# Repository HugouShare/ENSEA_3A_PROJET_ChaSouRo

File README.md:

# 🤖 ChaSouRo 🤖

## 📝 Rapport de projet

Pour consulter notre rapport de projet [cliquez ici](Documents/Rapport%20de%20projet.md)  

---

## 👨🏽 Équipe

<div align="left">

   **🙋‍♂️ [Hugo CARVALHO FONTES](https://github.com/HugouShare)**

   **🙋‍♂️ [Nelven THÉBAULT](https://github.com/NelvTheb)**

   **🙋‍♂️ [Hugo CORDI](https://github.com/Lynxlegrand)**

   **🙋‍♂️ [Arthur Cesar NJITCHOU NKWA](https://github.com/ArthurNjitchou)**

</div>

## ⚙️ Introduction

- Nous réalisons ce projet dans le cadre de notre dernière année d'étude en spécialité électronique et systèmes embarqués à l'[ENSEA](https://www.ensea.fr/fr) située à Cergy.
- Le but du projet est de réaliser deux robots : l'un étant le robot chat et l'autre le robot souris. Les deux robots évoluent ensuite de manière autonome sur une table. Le but du jeu est alors le suivant : le robot chat doit tenter d'attraper le robot souris qui doit donc tenter d'échapper au robot chat. Une fois que le robot chat attrape le robot souris, les rôles s'inversent et la partie continue. 

## 🎯 Missions & Objectifs

Les missions principales sont les suivantes (réparties selon différents niveaux) :
  - **Niveau 0 :**
    - Le robot se déplace
    - Il ne tombe pas de la table
  - **Niveau 1 :**
    - Il détecte et se dirige vers un objet
    - Ou s’en éloigne s’il n’est pas le chat
  - **Niveau 2 :**
    - Il change de comportement (proie/prédateur) après un contact
    - Il fonctionne avec plusieurs robots sur la table
  - **Niveau 3 :**
    - Il n’est pas affecté par les obstacles hors de la table
    - Il est donc capable de se localiser

Dans notre cas à nous, nous choisissons le niveau 1 voire potentiellement, selon notre avancement, le niveau 2.  

## ⌚ Timeline du projet  

```mermaid
%%{init: {"theme":"default", "themeVariables": {
  "primaryColor": "#4F46E5",
  "primaryTextColor": "#ffffff",
  "primaryBorderColor": "#312E81",
  "lineColor": "#6366F1",
  "secondaryColor": "#E0E7FF",
  "tertiaryColor": "#A5B4FC"
}}}%%

timeline
    section Phase 1 - conception du PCB
      Séance 1 : Point réunion + schéma architectural / BOM
      Séance 2 et 3 : Schéma électronique annoté
      Séance 4 : Corrections Schéma / BOM Finale
      Séance 5 : Point réunion + placement
      Séance 6 : Placement corrigé
      Séance 7 et 8 : Routage
      Séance 9 et 10 : Corrections Routage, export...
    section Phase 2 - mécanique 3D + prise en main et programmation des différents capteurs et actionneurs
      Séance 1 : Point réunion + architecture de subsomption + architecture schéma logicielle + soudure composants sur PCBs + vérification du bon fonctionnement des PCBs
      Séance 2 et 3 et 4 : Prise en main & programmation du LiDar + accéléromètre + écran OLED + module bluetooth avec développement application apk
      Séance 5 : Point réunion + vérification du bon fonctionnement des différents modules
      Séance 6 et 7 et 8 : Développement de l'odométrie + programmation des moteurs + 1x TOF puis 4x TOFs + modification de la structure mécanique du robot pour intégration des 4 TOFs et écran OLED
      Séance 9 et 10 : Impression 3D de la structure mécanique du robot + début de l'intégration des différents modules + finalisation de la programmation des 4x TOFs ensemble 
    section Phase 3 - Intégration, tests & vérifications
      Séance 1 et 2 : Point réunion + intégration, tests & vérifications
      Séance 3 : DEMONSTRATION FINALE
```

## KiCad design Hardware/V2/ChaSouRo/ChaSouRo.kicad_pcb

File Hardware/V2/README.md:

# Modifications sur la V1

- Problèmes sur la taille des empreintes pour les capacités >= 10uF -> Passage en 0603
- Changement pad sw wurth vers un connecteur (plus propre) -> JST_PH Batterie +/- (Pin_x2) en JS_PH_ Batterie +/- et +/IN du switch wurth (Pin_x4)
- Erreur sur un des deux drivers où les silkscreen des OUT1 et OUT2 sont inversé par rapport au pin (Quand on se place dans le sens avec TX4/RX4 du ST-Link -> Driver gauche)
- Ajout Silkscreen sur ST-Link pour simplifier la connexion
- Modification schématique/Nom du bon NMOSFET -> SQ2310ES
- Changement de la capacité de découplage du VDDA : 47uF -> 22uF
- Oublie des capacités pour limiter les rebonds sur USER1 et USER2 -> ajout de 0.1uF
- Inversion sur le PCB des RX3/TX3 sur les pins PB10/PB11 du STM32

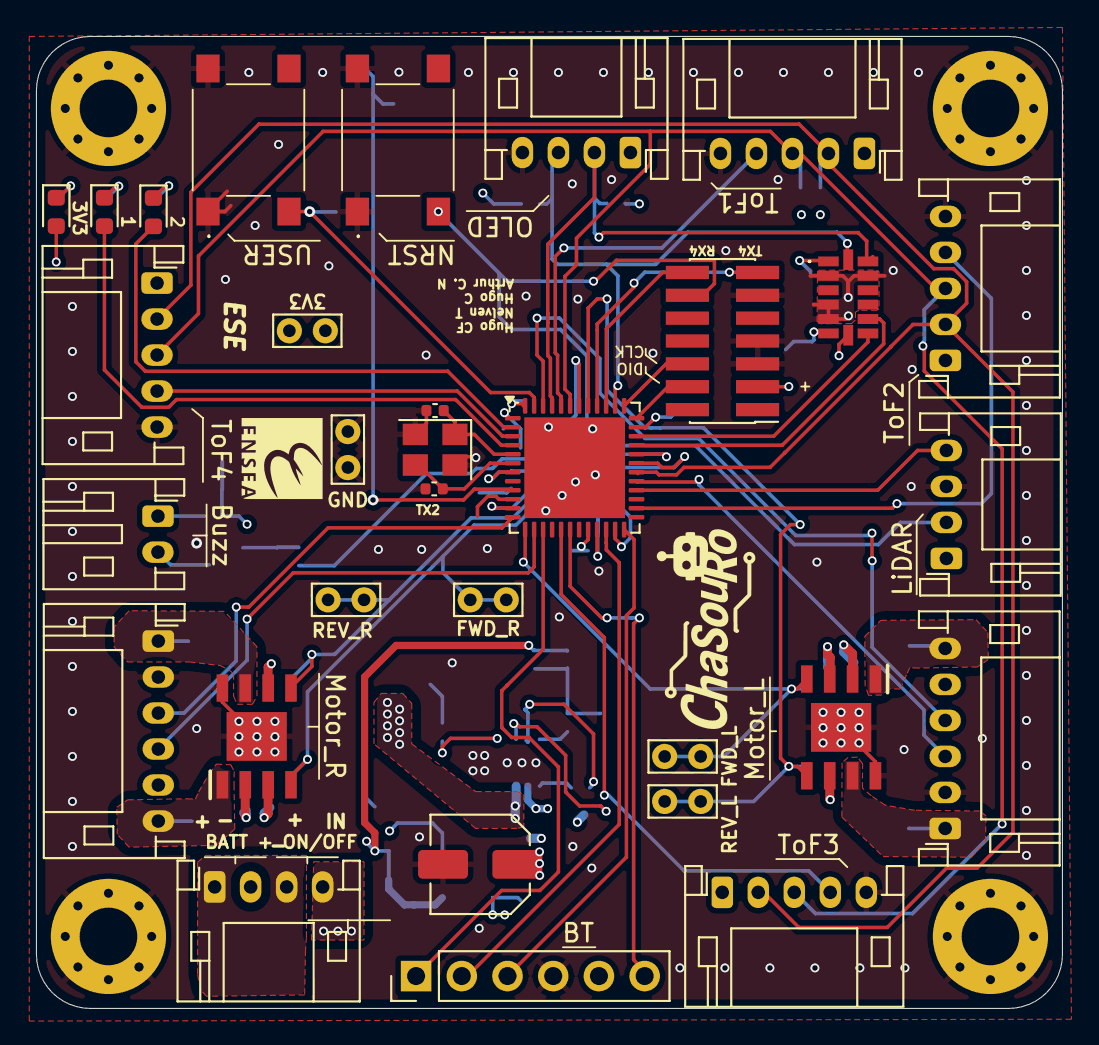
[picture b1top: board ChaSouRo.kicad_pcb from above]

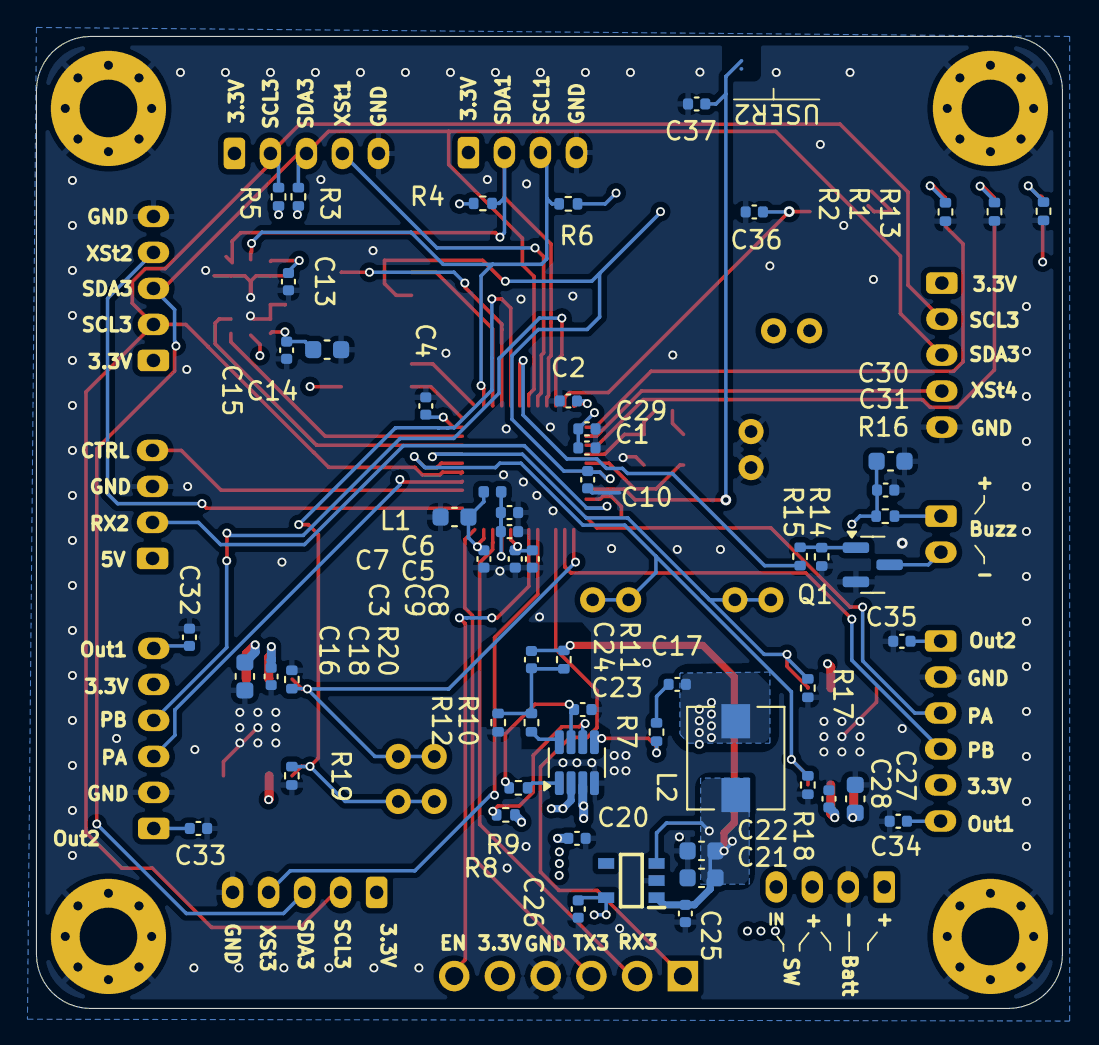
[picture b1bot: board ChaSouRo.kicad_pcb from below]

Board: 4 copper layers, 57.0 x 54.0 mm, 94 parts (59 on the bottom side), 60 nets.

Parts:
C1: 4.7u; C_0402_1005Metric
C2, C3, C4, C9, C10, C13, C15, C17, C18, C20, C23, C28, C29, C30, C32, C33, C34, C35, C36, C37: 0.1u; C_0402_1005Metric
C5: 10n; C_0402_1005Metric
C6, C8, C25, C26: 1u; C_0402_1005Metric
C7, C21, C22: 22u; C_0603_1608Metric
C11, C12: 22p; C_0402_1005Metric
C14, C16, C27, C31: 10u; C_0603_1608Metric
C19: 47u; C_Elec_5x5.4
C24: 15p; C_0402_1005Metric
D1: 1; LED_0603_1608Metric
D2: 2; LED_0603_1608Metric
D3: 3V3; LED_0603_1608Metric
H1, H2, H3, H4: MountingHole_Pad; MountingHole_3.2mm_M3_Pad_Via
IC1: ADXL343BCCZ-RL; ADXL343BCCZRL
IC2, IC4: ZXBM5210-SP-13; SOIC127P600X150-9N
IC3: MP1475DJ-LF-P; TSOT-23-8
IC5: BU33SD5WG-TR; SOT95P280X125-5N
J1: LiDAR; JST_PH_S4B-PH-K_1x04_P2.00mm_Horizontal
J2: OLED; JST_PH_S4B-PH-K_1x04_P2.00mm_Horizontal
J3: Conn_ST_STDC14; PinHeader_2x07_P1.27mm_Vertical_SMD
J4: BT; PinHeader_1x06_P2.54mm_Vertical
J5: ToF1; JST_PH_S5B-PH-K_1x05_P2.00mm_Horizontal
J6: ToF2; JST_PH_S5B-PH-K_1x05_P2.00mm_Horizontal
J7: ToF3; JST_PH_S5B-PH-K_1x05_P2.00mm_Horizontal
J8: ToF4; JST_PH_S5B-PH-K_1x05_P2.00mm_Horizontal
J9: Motor_L; JST_PH_S6B-PH-K_1x06_P2.00mm_Horizontal
J10: Motor_R; JST_PH_S6B-PH-K_1x06_P2.00mm_Horizontal
J11: BATT + ON/OFF; JST_PH_S4B-PH-K_1x04_P2.00mm_Horizontal
J12: Buzz; JST_PH_S2B-PH-K_1x02_P2.00mm_Horizontal
L1: 4.7n; L_0402_1005Metric
L2: 4.7u; L_Wuerth_HCI-5040
Q1: SQ2310ES; SOT-23
R1, R2, R13: 2.7k; R_0402_1005Metric
R3, R4, R5, R6: 4.7k; R_0402_1005Metric
R7: 20; R_0402_1005Metric
R8, R9, R14, R17, R18, R19, R20: 100k; R_0402_1005Metric
R10: 16k; R_0402_1005Metric
R11: 40.2k; R_0402_1005Metric
R12: 7.68k; R_0402_1005Metric
R15: 470; R_0402_1005Metric
R16: 100; R_0402_1005Metric
S1: NRST; 430182070816
S2: USER; 430182070816
TP2: GND; TestPoint_Bridge_Pitch2.0mm_Drill0.7mm
TP3: 3V3; TestPoint_Bridge_Pitch2.0mm_Drill0.7mm
TP4: FWD_L; TestPoint_Bridge_Pitch2.0mm_Drill0.7mm
TP5: REV_L; TestPoint_Bridge_Pitch2.0mm_Drill0.7mm
TP6: FWD_R; TestPoint_Bridge_Pitch2.0mm_Drill0.7mm
TP7: REV_R; TestPoint_Bridge_Pitch2.0mm_Drill0.7mm
U1: STM32G431CBUx; QFN-48-1EP_7x7mm_P0.5mm_EP5.6x5.6mm
Y1: Crystal_GND24_Small; Crystal_SMD_3225-4Pin_3.2x2.5mm

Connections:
+3.3V: C1.1, C2.1, C3.1, C4.1, C7.1, C8.1, C9.1, C13.1, C14.1, C15.1, C26.1, C29.1, D3.2 (A), IC1.1 (VDD_I/O), IC1.6 (VS), IC1.7 (~CS), IC5.5 (VOUT), J2.1, J3.3 (VCC), J4.5, J5.1, J6.1, J7.1, J8.1, J9.5, J10.5, L1.2, R3.2, R4.2, R5.2, R6.2, TP3.1, U1.1 (VBAT), U1.20 (VREF+), U1.23 (VDD), U1.35 (VDD), U1.48 (VDD)
+3.3VA: C5.1, C6.1, L1.1, U1.21 (VDDA)
+5V: C21.1, C22.1, C24.1, C25.1, C30.1, C31.1, IC5.1 (VIN), IC5.3 (STBY), J1.1, L2.2, R11.1, R16.2
+7.5V: C16.1, C18.1, C19.1, C20.1, C27.1, C28.1, IC2.2 (VM), IC2.3 (VDD), IC2.6 (VREF), IC3.2 (IN), IC4.2 (VM), IC4.3 (VDD), IC4.6 (VREF), J11.4, R8.1
/D1: D1.2 (A), U1.4 (PC15)
/D2: D2.2 (A), U1.2 (PC13)
/Power&Control/FB: IC3.8 (FB), R10.2
/Power&Control/OUT_2_L: C33.1, IC2.7 (OUT_2), J9.1
/Power&Control/OUT_2_R: C35.1, IC4.7 (OUT_2), J10.1
/Power&Control/R_Bridge: C24.2, R10.1, R11.2, R12.1
/Sensors&periphs/Buzz+: J12.1, R16.1
/Sensors&periphs/D_Buzz-: J12.2, Q1.3 (D)
/Sensors&periphs/G_Q1: Q1.1 (G), R14.1, R15.2
/USER1: C36.1, S2.2, U1.47 (PB9)
Buzzer: R15.1, U1.42 (PB4)
ENC_PA_L: J9.3, U1.29 (PC6)
ENC_PA_R: J10.3, U1.12 (PA4)
ENC_PB_L: J9.4, U1.46 (PB8)
ENC_PB_R: J10.4, U1.14 (PA6)
EN_BT: J4.6, U1.18 (PB1)
EN/SYNC: IC3.6 (EN/SYNC), R8.2
FWD_L: IC2.4 (FWD), R20.1, TP4.1, U1.13 (PA5)
FWD_R: IC4.4 (FWD), R18.1, TP6.1, U1.31 (PA9)
GND: C1.2, C2.2, C3.2, C4.2, C5.2, C6.2, C7.2, C8.2, C9.2, C10.2, C11.2, C12.2, C13.2, C14.2, C15.2, C16.2, C18.2, C19.2, C20.2, C21.2, C22.2, C23.2, C25.2, C26.2, C27.2, C28.2, C29.2, C30.2, C31.2, C32.2, C33.2, C34.2, C35.2, C36.2, C37.2, H1.1, H2.1, H3.1, H4.1, IC1.2 (GND_1), IC1.4 (GND_2), IC1.5 (GND_3), IC1.12 (SDO/ALT_ADDRESS), IC2.8 (GND), IC2.9 (EP), IC3.4 (GND), IC4.8 (GND), IC4.9 (EP), IC5.2 (GND), J1.3, J2.4, J3.5 (GND), J3.7 (GND), J3.11 (GNDDetect), J4.4, J5.5, J6.5, J7.5, J8.5, J9.2, J10.2, J11.2, Q1.2 (S), R1.1, R2.1, R12.2, R13.1, R14.2, R17.2, R18.2, R19.2, R20.2, S1.1, S2.1, TP2.1, U1.49 (VSS), Y1.2, Y1.4
INT_XL1: IC1.8 (INT1), U1.34 (PA12)
INT_XL2: IC1.9 (INT2), U1.33 (PA11)
LED_STATE: J4.1, U1.15 (PA7)
M_CTRL: J1.4, U1.28 (PB15)
NRST: C10.1, J3.12 (~RST), S1.2, U1.7 (PG10)
unnamed: C17.1, R7.2
unnamed: D1.1 (K), R1.2
unnamed: D2.1 (K), R2.2
unnamed: D3.1 (K), R13.2
unnamed: IC3.5 (BST), R7.1
unnamed: C23.1, IC3.7 (VCC), R9.2
unnamed: C11.1, U1.5 (PF0), Y1.1
unnamed: C12.1, U1.6 (PF1), Y1.3
OUT_1_L: C32.1, IC2.1 (OUT_1), J9.6
OUT_1_R: C34.1, IC4.1 (OUT_1), J10.6
PG: IC3.1 (PG), R9.1
REV_L: IC2.5 (REV), R19.1, TP5.1, U1.41 (PB3)
REV_R: IC4.5 (REV), R17.1, TP7.1, U1.32 (PA10)
RX2: J1.2, U1.11 (PA3)
RX3: J4.2, U1.22 (PB10)
RX4: J3.13 (VCP_RX), U1.40 (PC11)
SCL1: IC1.14 (SCL/SCLK), J2.3, R6.1, U1.38 (PA15)
SCL3: J5.2, J6.2, J7.2, J8.2, R5.1, U1.30 (PA8)
SDA1: IC1.13 (SDA/SDI/SDIO), J2.2, R4.1, U1.45 (PB7)
SDA3: J5.3, J6.3, J7.3, J8.3, R3.1, U1.43 (PB5)
SW: C17.2, IC3.3 (SW), L2.1
SWCLK: J3.6 (JCLK/SWCLK), U1.37 (PA14)
SWDIO: J3.4 (JTMS/SWDIO), U1.36 (PA13)
TX3: J4.3, U1.24 (PB11)
TX4: J3.14 (VCP_TX), U1.39 (PC10)
USER2: C37.1, U1.9 (PA1)
VBAT+: J11.1, J11.3
XShunt1: J5.4, U1.44 (PB6)
XShunt2: J6.4, U1.26 (PB13)
XShunt3: J7.4, U1.17 (PB0)
XShunt4: J8.4, U1.3 (PC14)

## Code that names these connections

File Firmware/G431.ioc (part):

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Mcu.Name=STM32G431C(6-8-B)Ux
Mcu.Package=UFQFPN48
Mcu.UserName=STM32G431CBUx
PA1.GPIOParameters=GPIO_Label
PA1.GPIO_Label=USER2
PA1.Signal=GPXTI1
PA10.GPIOParameters=GPIO_Label
PA10.GPIO_Label=REV_R
PA10.Signal=S_TIM2_CH4
PA11.GPIOParameters=GPIO_Label
PA11.GPIO_Label=INT_XL2
PA11.Signal=GPXTI11
PA12.GPIOParameters=GPIO_Label
PA12.GPIO_Label=INT_XL1
PA12.Signal=GPXTI12
PA13.Mode=Serial_Wire
PA13.Signal=SYS_JTMS-SWDIO
PA14.Mode=Serial_Wire
PA14.Signal=SYS_JTCK-SWCLK
PA15.Mode=I2C
PA15.Signal=I2C1_SCL
PA2.Mode=Asynchronous
PA2.Signal=USART2_TX
PA3.Mode=Asynchronous
PA3.Signal=USART2_RX
PA4.GPIOParameters=GPIO_Label
PA4.GPIO_Label=ENC_PA_R
PA4.Signal=S_TIM3_CH2
PA5.GPIOParameters=GPIO_Label
PA5.GPIO_Label=FWD_L
PA5.Signal=S_TIM2_CH1
PA6.GPIOParameters=GPIO_Label
PA6.GPIO_Label=ENC_PB_R
PA6.Signal=S_TIM3_CH1
PA7.GPIOParameters=GPIO_Label
PA7.GPIO_Label=LED_STATE
PA7.Signal=GPIO_Input
PA8.Mode=I2C
PA8.Signal=I2C3_SCL
PA9.GPIOParameters=GPIO_Label
PA9.GPIO_Label=FWD_R
PA9.Signal=S_TIM2_CH3
PB0.GPIOParameters=GPIO_Label
PB0.GPIO_Label=XShunt3
PB0.Signal=GPXTI0
PB1.GPIOParameters=GPIO_Label
PB1.GPIO_Label=EN_BT
PB1.Signal=GPIO_Output
PB10.Mode=Asynchronous
PB10.Signal=USART3_TX
PB11.Mode=Asynchronous
PB11.Signal=USART3_RX
PB13.GPIOParameters=GPIO_Label
PB13.GPIO_Label=XShunt2
PB13.Signal=GPXTI13
PB15.GPIOParameters=GPIO_Label
PB15.GPIO_Label=M_CTRL
PB15.Signal=S_TIM15_CH2
PB3.GPIOParameters=GPIO_Label
PB3.GPIO_Label=REV_L
PB3.Signal=S_TIM2_CH2
PB4.GPIOParameters=GPIO_Label
PB4.GPIO_Label=Buzzer
PB4.Signal=S_TIM16_CH1
PB5.Mode=I2C
PB5.Signal=I2C3_SDA
PB6.GPIOParameters=GPIO_Label
PB6.GPIO_Label=XShunt1
PB6.Signal=GPXTI6
PB7.Mode=I2C
PB7.Signal=I2C1_SDA
PB8-BOOT0.GPIOParameters=GPIO_Label
PB8-BOOT0.GPIO_Label=ENC_PB_L
PB8-BOOT0.Signal=S_TIM8_CH2
PB9.GPIOParameters=GPIO_Label
PB9.GPIO_Label=USER1
PB9.Signal=GPXTI9
PC10.Mode=Asynchronous
PC10.Signal=UART4_TX
PC11.Mode=Asynchronous
PC11.Signal=UART4_RX
PC13.GPIOParameters=GPIO_Label
PC13.GPIO_Label=LED_D2
PC13.Signal=GPIO_Output
PC14-OSC32_IN.GPIOParameters=GPIO_Label
PC14-OSC32_IN.GPIO_Label=XShunt4
PC14-OSC32_IN.Signal=GPXTI14
PC15-OSC32_OUT.GPIOParameters=GPIO_Label
PC15-OSC32_OUT.GPIO_Label=LED_D1
PC15-OSC32_OUT.Signal=GPIO_Output
PC6.GPIOParameters=GPIO_Label
PC6.GPIO_Label=ENC_PA_L
PC6.Signal=S_TIM8_CH1
PF0-OSC_IN.Mode=HSE-External-Oscillator
PF0-OSC_IN.Signal=RCC_OSC_IN
PF1-OSC_OUT.Mode=HSE-External-Oscillator
PF1-OSC_OUT.Signal=RCC_OSC_OUT
RCC.HSE_VALUE=8000000
RCC.SYSCLKFreq_VALUE=16000000
board=custom

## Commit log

2025-09-08 creation of the repository
2025-09-10 adding of docs
2025-09-10 adding of all the datasheets
2025-09-10 ajout du schéma fonctionnel
2025-09-11 Ajout lib schematic
2025-09-12 ajout tof
2025-09-12 maj 3D
2025-09-16 ajout architecture
2025-09-16 ajout schéma fonctionnel maj
2025-09-26 Remove tracked .DS_Store files
2025-09-26 Add .gitignore to ignore .DS_Store
2025-09-26 Ajout PCB
2025-09-28 maj PCB
2025-09-28 maj PCB commande
2025-09-29 ajout du code du lidar pas fini
2025-09-30 code fonctionne presque
2025-10-01 check pcb LF
2025-10-01 ajout d'un SW PCB
2025-10-01 problème d'angles morts corrigé
2025-10-07 Ajout code OLED
2025-10-07 Ajout code ENC
2025-10-13 Code fonctionnel clean sans FreeRTOS
2025-10-13 Code fonctionnel clean sans FreeRTOS 2
2025-10-13 passage sous FreeRTOS réussi
2025-10-13 notes actualisées
2025-10-22 Ajout du .ioc
    .ioc à utiliser pour créer le projet cubeIDE avec tous les pins configurés.
2025-10-22 modif gitignore
2025-10-25 Ajout V2 PCB
2025-11-12 lidar+enc integre
2025-11-12 suuuu
2025-11-18 code avec 2 encodeurs
2025-11-18 odometrie finie, à tester
2025-11-19 Create LICENSE
2025-11-19 ajout oled RTOS G431
2025-11-19 Code ADXL345
    Code accéléromètre ADXL345
2025-11-19 code encodeurs fini
2025-11-19 dossier meca
2025-11-19 Ajout code ADXL
2025-11-25 commit du code final, LIDAR + encodeurs a optimiser
2025-11-25 commit du code final, LIDAR + encodeurs a optimiser2
2025-11-26 ajout driverMotor code
    + modif du gitignore
2025-11-26 code final
2025-11-26 ajout readme
2025-11-26 modif pcb
2025-12-01 modif V2 PCB
2025-12-01 modif readme changements
2025-12-02 ajout meca + gcodes
2025-12-02 ajout dma oled
2025-12-03 code LIDAR + enc allégé
2025-12-03 maj oled dma (previous not done)
2025-12-03 modif DriverMotor FreeRTOS non bloquant propre
2025-12-03 code allégé intégré
2025-12-09 code optimisé
2025-12-10 modif drivermotor
2025-12-10 add of vl53l0x code
2025-12-11 code integre : lidar+enc+moteurs+odom
2025-12-11 code integre : lidar+enc+moteurs+odom+ecran(a finir)
2025-12-17 Add task report document
2025-12-26 Update project timeline and activity log sections
2025-12-26 restructuration
2025-12-26 Update project report with new task list and context
2025-12-26 Update project report with context and tasks
    Added project context and task responsibilities.
2025-12-26 Change project description link to PDF
    Updated project description link from .md to .pdf format.
2025-12-26 Fix link formatting in project report
2025-12-26 Fix links in project report document
2025-12-26 Update project report with functional diagram and tasks
    Added a functional diagram and individual task report for team members.
2025-12-26 Fix formatting and grammar in project report
    Corrected grammatical errors and improved formatting in the project report.
2025-12-26 Update project level selection details
    Clarify project level selection in README.
2025-12-26 Update README with project level selection details
    Added a note about project level selection.
2026-01-14 code control pas fini
2026-01-15 ajout control
2026-01-15 maj hardware v2
2026-01-15 control fini
2026-01-15 maj code final
2026-01-16 version fonctionnelle
2026-01-16 maj code demonstration classe
2026-01-24 Update Rapport de projet.md
    Tâches réalisées au sein du projet par Arthur
2026-01-24 Update ici_se_trouve_la_meca.txt
    Détails partie mécanique
2026-01-24 Update Rapport Mecanique.md
    Explications partie méca
2026-01-24 Update Rapport Mecanique.md
    Intégration image méca
2026-01-25 maj rapport
2026-01-25 Update project title in README
2026-01-25 Add project report section to README
    Added a project report section with a link to the document.
2026-01-25 Update Rapport de projet.md
    Correction images
2026-01-25 maj finale
2026-01-25 Update project report with BOOT0 usage warnings
    Added important note regarding the use of PB4 (BOOT0) and its implications for future projects. Emphasized the risks associated with using BOOT0 on STM32 microcontrollers.
2026-01-25 Fix video file paths in project report
    Updated video file paths to include '.mp4' extension for clarity.
2026-01-26 Update error video rapport
